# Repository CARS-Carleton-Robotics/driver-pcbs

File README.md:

# Drone driver PCBs
This repository contains the pcbs designed and fabricated for Carleton Robotics Club's autonomous drone swarm project. Designed using KiCad.

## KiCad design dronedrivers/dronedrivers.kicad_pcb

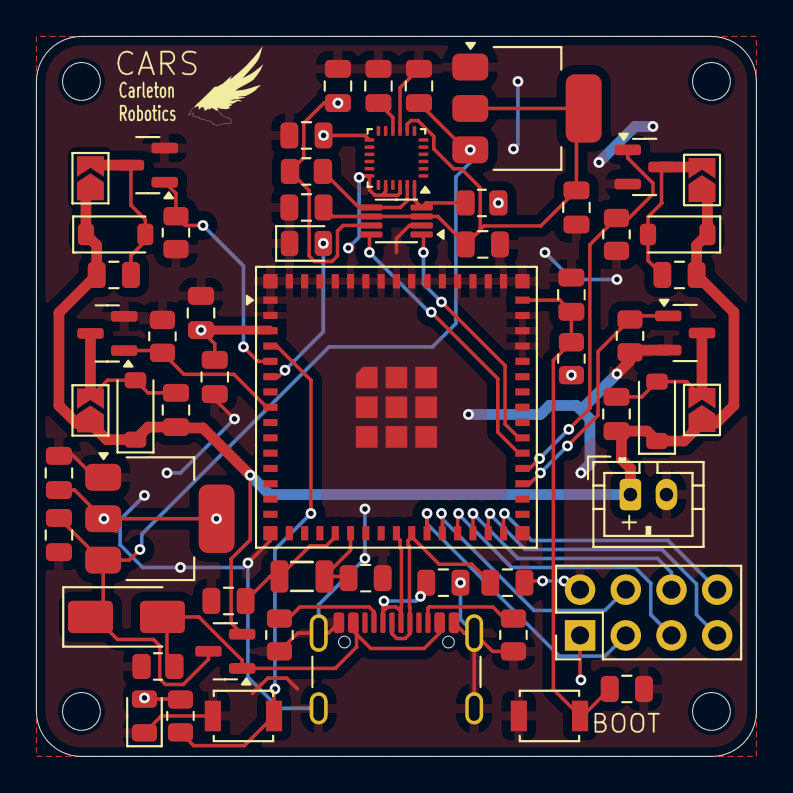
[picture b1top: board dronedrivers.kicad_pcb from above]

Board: 2 copper layers, 40.0 x 40.0 mm, 63 parts (0 on the bottom side), 34 nets.

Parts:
C1, C13: 22uF; C_0805_2012Metric
C2: 100nF; C_0805_2012Metric
C3, C7, C16, C17: 0.1uF; C_0805_2012Metric
C4, C9, C10, C11, C12: 1uF; C_0805_2012Metric
C5, C6: 47pF; C_0805_2012Metric
C8, C14, C15, C20, C21: 10uF; C_0805_2012Metric
C18, C19: 12pF; C_0805_2012Metric
D1, D3, D4, D5: 1N4148W; D_SOD-123
D2: SS34; D_SMA
D6, D7: LED; LED_0805_2012Metric
H1, H2, H3, H4: MountingHole; MountingHole_2.1mm
J1, J4, J5, J6: MOTOR; SolderJumper-2_P1.3mm_Open_TrianglePad1.0x1.5mm
J2: BATT; JST_PH_B2B-PH-K_1x02_P2.00mm_Vertical
J7: Conn_02x04_Top_Bottom; PinHeader_2x04_P2.54mm_Vertical
J9: USB_C_Receptacle_USB2.0_16P; USB_C_Receptacle_GCT_USB4105-xx-A_16P_TopMnt_Horizontal
Q1, Q3, Q4, Q5: AO3400A; SOT-23
Q2: AO3401A; SOT-23
R1, R2, R3, R4, R5, R6, R9, R10: 10K; R_0805_2012Metric
R7, R8: 5.1K; R_0805_2012Metric
R11: 100K; R_0805_2012Metric
SW1: RST; SW_SPST_B3U-1000P
SW2: BOOT; SW_SPST_B3U-1000P
U2: ESP32-S3-MINI-1U; ESP32-S2-MINI-1U
U3: TXB0102DCU; VSSOP-8_2.3x2mm_P0.5mm
U4: ICM-20948; InvenSense_QFN-24_3x3mm_P0.4mm
U5: AMS1117-1.8; SOT-223-3_TabPin2
U6: AMS1117-3.3; SOT-223-3_TabPin2
X1: Q13FC1350000400; FC-135R_L3.2-W1.5

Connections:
+1V8: C15.1, C17.1, C21.2, U3.3 (VCCA), U3.6 (OE), U4.8 (VDDIO), U5.2 (VO)
+3.3V: C1.1, C2.1, C13.1, C16.1, C20.2, D6.2 (A), J7.1, R1.1, R3.1, R9.2, R10.2, U2.3 (3V3), U3.7 (VCCB), U4.13 (VDD), U6.2 (VO)
+BATT: C9.1, C10.1, C11.1, C12.1, D1.1 (K), D3.1 (K), D4.1 (K), D5.1 (K), J1.1, J2.1, J4.1, J5.1, J6.1, Q2.2 (S)
D+: C6.1, J9.A6 (D+), J9.B6 (D+), U2.24 (USB_D+)
D-: C5.1, J9.A7 (D-), J9.B7 (D-), U2.23 (USB_D-)
EN: C4.1, C7.2, R1.2, SW1.2, U2.45 (EN)
GND: C1.2, C2.2, C3.2, C4.2, C5.2, C6.2, C7.1, C8.2, C13.2, C14.2, C15.2, C16.2, C17.2, C18.2, C19.2, C20.1, C21.1, D6.1 (K), D7.1 (K), J2.2, J7.2, J9.A1 (GND), J9.A12 (GND), J9.B1 (GND), J9.B12 (GND), J9.S1 (SHIELD), Q1.2 (S), Q3.2 (S), Q4.2 (S), Q5.2 (S), R2.2, R4.2, R5.2, R6.2, R7.2, R8.2, R11.2, SW1.1, SW2.1, U2.1 (GND), U2.2 (GND), U2.41 (IO45), U2.42 (GND), U2.43 (GND), U2.44 (IO46), U2.46 (GND), U2.47 (GND), U2.48 (GND), U2.49 (GND), U2.50 (GND), U2.51 (GND), U2.52 (GND), U2.53 (GND), U2.54 (GND), U2.55 (GND), U2.56 (GND), U2.57 (GND), U2.58 (GND), U2.59 (GND), U2.60 (GND), U2.61 (GND), U2.62 (GND), U2.63 (GND), U2.64 (GND), U2.65 (GND), U3.2 (GND), U4.9 (SDO/AD0), U4.18 (GND), U4.20 (GND), U4.22 (~CS), U5.1 (GND), U6.1 (GND)
IO0: R3.2, SW2.2, U2.4 (IO0)
IO1: Q1.1 (G), R2.1, U2.5 (IO1)
IO2: Q3.1 (G), R4.1, U2.8 (IO4)
IO3: Q4.1 (G), R5.1, U2.33 (IO37)
IO4: Q5.1 (G), R6.1, U2.34 (IO38)
IO5: U2.36 (IO40), U3.1 (B2)
IO6: U2.35 (IO39), U3.8 (B1)
IO9: J7.3, U2.25 (IO21)
IO10: J7.4, U2.26 (IO26)
IO11: J7.5, U2.27 (IO47)
IO12: J7.6, U2.28 (IO33)
IO13: J7.7, U2.29 (IO34)
IO14: J7.8, U2.30 (IO48)
unnamed: C9.2, D1.2 (A), J1.2, Q1.3 (D)
unnamed: D2.2 (A), J9.A4 (VBUS), J9.A9 (VBUS), J9.B4 (VBUS), J9.B9 (VBUS), Q2.1 (G), R11.1
unnamed: C10.2, D3.2 (A), J4.2, Q3.3 (D)
unnamed: C11.2, D4.2 (A), J5.2, Q4.3 (D)
unnamed: C12.2, D5.2 (A), J6.2, Q5.3 (D)
unnamed: D7.2 (A), U2.6 (IO2)
unnamed: J9.A5 (CC1), R7.1
unnamed: J9.B5 (CC2), R8.1
unnamed: C19.1, U2.19 (IO15), X1.1
unnamed: C18.1, U2.20 (IO16), X1.2
unnamed: R10.1, U3.5 (A1), U4.23 (SCL/SCLK)
unnamed: R9.1, U3.4 (A2), U4.24 (SDA/SDI)
unnamed: C3.1, U4.10 (REGOUT)
VIN: C8.1, C14.1, D2.1 (K), Q2.3 (D), U5.3 (VI), U6.3 (VI)

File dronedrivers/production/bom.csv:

Designator,Footprint,Quantity,Value,LCSC Part #
"C1, C13, C5, C6",0805,4,22uF,
"C10, C11, C12, C4, C9",0805,5,1uF,
"C14, C15, C8",0805,3,10uF,
"C16, C17, C3, C7",0805,4,0.1uF,
C2,0805,1,100nF,
"D1, D3, D4, D5",D_SOD-123,4,1N4148W,
D2,D_SMA,1,SS34,
"J1, J4, J5, J6",SolderJumper-2_P1.3mm_Open_TrianglePad1.0x1.5mm,4,MOTOR,
J2,JST_PH_B2B-PH-K_1x02_P2.00mm_Vertical,1,BATT,
"J3, J8",PinHeader_1x04_P2.54mm_Vertical,2,UART,
J9,USB_C_Receptacle_GCT_USB4105-xx-A_16P_TopMnt_Horizontal,1,USB_C_Receptacle_USB2.0_16P,
"Q1, Q3, Q4, Q5",SOT-23,4,AO3400A,
Q2,SOT-23,1,AO3401A,
"R1, R2, R3, R4, R5, R6",0805,6,10K,
"R7, R8",0805,2,5.1K,
SW1,SW_SPST_B3U-1000P,1,RST,
SW2,SW_SPST_B3U-1000P,1,BOOT,
U1,ESP32-S3-WROOM-1,1,ESP32-S3-WROOM-1,
U3,SOIC-14_3.9x8.7mm_P1.27mm,1,TXB0104D,
U4,InvenSense_QFN-24_3x3mm_P0.4mm,1,ICM-20948,
U5,SOT-223-3_TabPin2,1,AMS1117-1.8,
U6,SOT-223-3_TabPin2,1,AMS1117-3.3,

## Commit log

2025-04-05 init
2025-04-13 reworked driver pcb
